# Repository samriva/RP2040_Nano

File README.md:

# RP2040_Nano
Respberry_Pi_RP2040 core board

Size 24*26mm # create by KiCAD 5.1.9

Included 128Mb spi flash, with all I/O pins out by 0.35mm BTB connectors for your own base board.

...

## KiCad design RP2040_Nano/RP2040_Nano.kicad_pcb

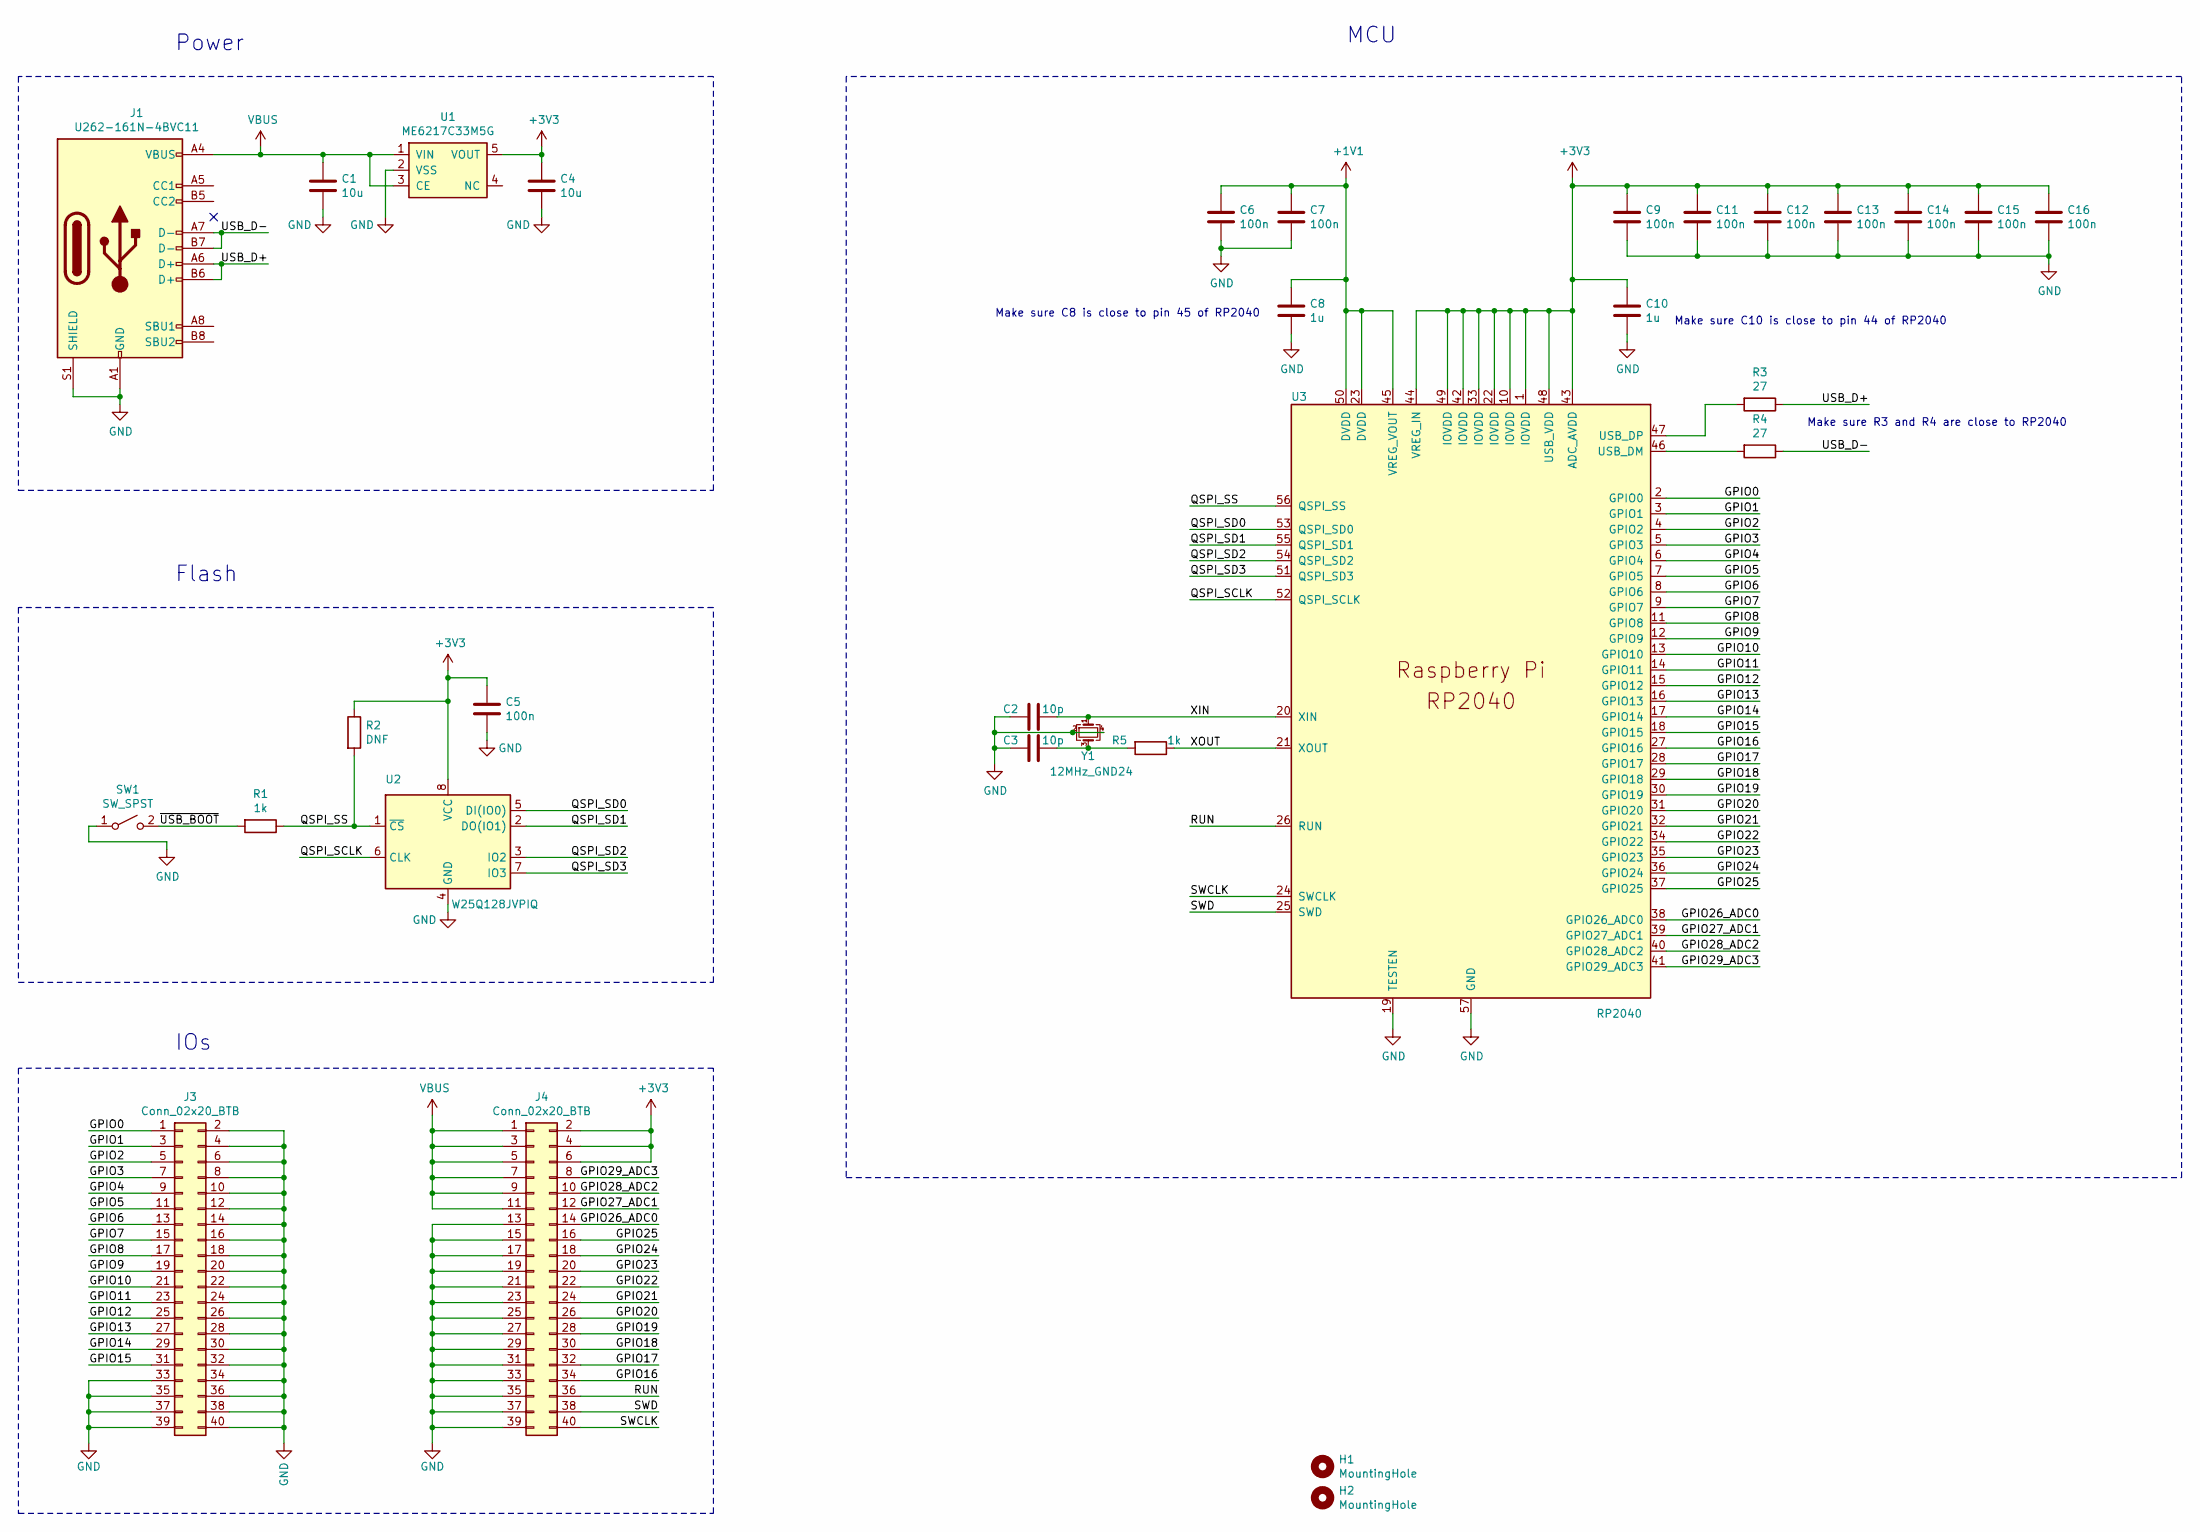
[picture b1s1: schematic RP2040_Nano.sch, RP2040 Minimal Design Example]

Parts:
C1, C4: 10u; C_0805_2012Metric
C2, C3: 10p; C_0402_1005Metric
C5, C6, C7, C9, C11, C12, C13, C14, C15, C16: 100n; C_0402_1005Metric
C8, C10: 1u; C_0402_1005Metric
H1, H2: MountingHole; MountingHole_2.7mm_M2.5
J1: U262-161N-4BVC11; USB_C_Receptacle_XKB_U262-16XN-4BVC11
J3, J4: Conn_02x20_BTB; Hirose_BM24_BM24-40DS-2-0.35V_2x20_P0.35mm_PowerPin2_Vertic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
R1, R5: 1k; C_0402_1005Metric
R2: DNF; C_0402_1005Metric
R3, R4: 27; C_0402_1005Metric
SW1: SW_SPST; SW_Push_1P1T_NO_Vertical_Wuerth_434133025816
U1: ME6217C33M5G; SOT-23-5
U2: W25Q128JVPIQ; WSON-8-1EP_6x5mm_P1.27mm_EP3.4x4mm
U3: RP2040; RP2040-QFN-56
Y1: 12MHz_GND24; Crystal_SMD_2520-4Pin_2.5x2.0mm

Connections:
+1V1: C6.1, C7.1, C8.1, U3.23 (DVDD), U3.45 (VREG_VOUT), U3.50 (DVDD)
+3V3: C4.1, C5.1, C9.1, C10.1, C11.1, C12.1, C13.1, C14.1, C15.1, C16.1, J4.2, J4.4, J4.6, R2.1, U1.5 (VOUT), U2.8 (VCC), U3.1 (IOVDD), U3.10 (IOVDD), U3.22 (IOVDD), U3.33 (IOVDD), U3.42 (IOVDD), U3.43 (ADC_AVDD), U3.44 (VREG_IN), U3.48 (USB_VDD), U3.49 (IOVDD)
/GPIO0: J3.1, U3.2 (GPIO0)
/GPIO1: J3.3, U3.3 (GPIO1)
/GPIO2: J3.5, U3.4 (GPIO2)
/GPIO3: J3.7, U3.5 (GPIO3)
/GPIO4: J3.9, U3.6 (GPIO4)
/GPIO5: J3.11, U3.7 (GPIO5)
/GPIO6: J3.13, U3.8 (GPIO6)
/GPIO7: J3.15, U3.9 (GPIO7)
/GPIO8: J3.17, U3.11 (GPIO8)
/GPIO9: J3.19, U3.12 (GPIO9)
/GPIO10: J3.21, U3.13 (GPIO10)
/GPIO11: J3.23, U3.14 (GPIO11)
/GPIO12: J3.25, U3.15 (GPIO12)
/GPIO13: J3.27, U3.16 (GPIO13)
/GPIO14: J3.29, U3.17 (GPIO14)
/GPIO15: J3.31, U3.18 (GPIO15)
/GPIO16: J4.34, U3.27 (GPIO16)
/GPIO17: J4.32, U3.28 (GPIO17)
/GPIO18: J4.30, U3.29 (GPIO18)
/GPIO19: J4.28, U3.30 (GPIO19)
/GPIO20: J4.26, U3.31 (GPIO20)
/GPIO21: J4.24, U3.32 (GPIO21)
/GPIO22: J4.22, U3.34 (GPIO22)
/GPIO23: J4.20, U3.35 (GPIO23)
/GPIO24: J4.18, U3.36 (GPIO24)
/GPIO25: J4.16, U3.37 (GPIO25)
/GPIO26_ADC0: J4.14, U3.38 (GPIO26_ADC0)
/GPIO27_ADC1: J4.12, U3.39 (GPIO27_ADC1)
/GPIO28_ADC2: J4.10, U3.40 (GPIO28_ADC2)
/GPIO29_ADC3: J4.8, U3.41 (GPIO29_ADC3)
/QSPI_SCLK: U2.6 (CLK), U3.52 (QSPI_SCLK)
/QSPI_SD0: U2.5 (DI(IO0)), U3.53 (QSPI_SD0)
/QSPI_SD1: U2.2 (DO(IO1)), U3.55 (QSPI_SD1)
/QSPI_SD2: U2.3 (IO2), U3.54 (QSPI_SD2)
/QSPI_SD3: U2.7 (IO3), U3.51 (QSPI_SD3)
/QSPI_SS: R1.1, R2.2, U2.1 (~CS), U3.56 (QSPI_SS)
/RUN: J4.36, U3.26 (RUN)
/SWCLK: J4.40, U3.24 (SWCLK)
/SWD: J4.38, U3.25 (SWD)
/USB_D+: J1.A6 (D+), J1.B6 (D+), R3.1
/USB_D-: J1.A7 (D-), J1.B7 (D-), R4.1
/XIN: C2.1, U3.20 (XIN), Y1.1
/XOUT: R5.1, U3.21 (XOUT)
/~USB_BOOT: R1.2, SW1.2 (B)
GND: C1.2, C2.2, C3.2, C4.2, C5.2, C6.2, C7.2, C8.2, C9.2, C10.2, C11.2, C12.2, C13.2, C14.2, C15.2, C16.2, J1.A1 (GND), J1.A12 (GND), J1.B1 (GND), J1.B12 (GND), J1.S1 (SHIELD), J3.2, J3.4, J3.6, J3.8, J3.10, J3.12, J3.14, J3.16, J3.18, J3.20, J3.22, J3.24, J3.26, J3.28, J3.30, J3.32, J3.33, J3.34, J3.35, J3.36, J3.37, J3.38, J3.39, J3.40, J3.41, J3.42, J4.13, J4.15, J4.17, J4.19, J4.21, J4.23, J4.25, J4.27, J4.29, J4.31, J4.33, J4.35, J4.37, J4.39, J4.41, J4.42, SW1.1 (A), U1.2 (VSS), U2.4 (GND), U2.9, U3.19 (TESTEN), U3.57 (GND), Y1.2, Y1.4
unnamed: C3.1, R5.2, Y1.3
unnamed: R3.2, U3.47 (USB_DP)
unnamed: R4.2, U3.46 (USB_DM)
VBUS: C1.1, J1.A4 (VBUS), J1.A9 (VBUS), J1.B4 (VBUS), J1.B9 (VBUS), J4.1, J4.3, J4.5, J4.7, J4.9, J4.11, U1.1 (VIN), U1.3 (CE)

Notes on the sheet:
Make sure C10 is close to pin 44 of RP2040
Make sure C8 is close to pin 45 of RP2040
MCU
Power
IOs
Make sure R3 and R4 are close to RP2040
Flash

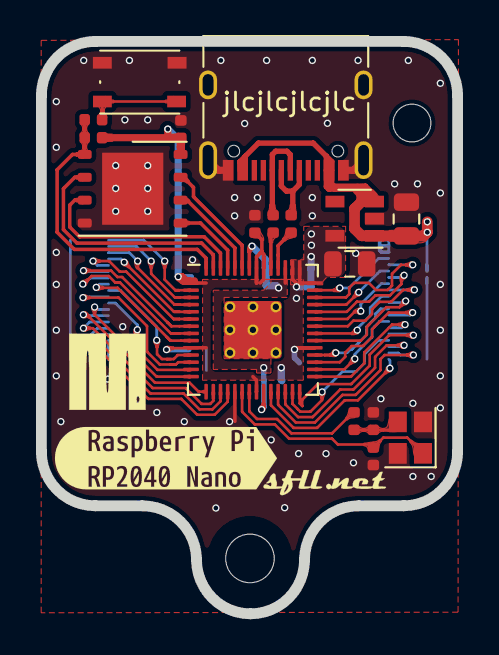
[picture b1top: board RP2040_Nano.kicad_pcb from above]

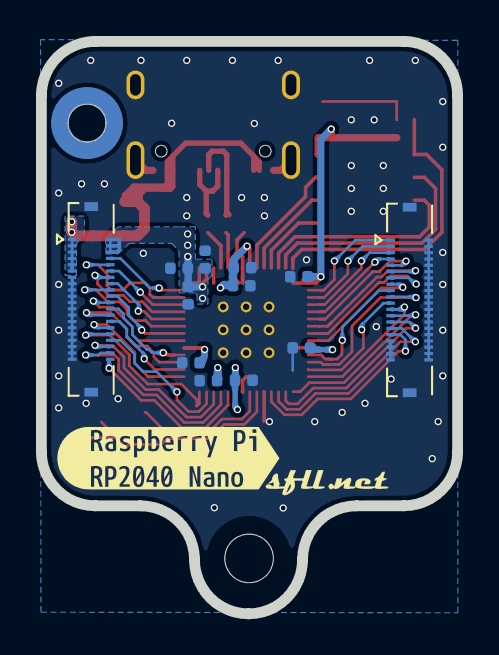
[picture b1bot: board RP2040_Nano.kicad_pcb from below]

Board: 2 copper layers, 23.1 x 31.8 mm, 33 parts (14 on the bottom side), 51 nets.

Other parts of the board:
M2: Mounting_Wuerth_WA-SMSI-M1.6_H1.5mm_9774015633
svg2mod, svg2mod#2: G***; label
